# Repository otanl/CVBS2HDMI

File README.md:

# CVBS2HDMI — composite NTSC to HDMI on a Tang Nano 20K

English | [日本語](README.ja.md)

**v0.1**

> **Status.** What has been tested is the firmware together with the board as built, v0.1
> (tag `v0.1`). The board design now in `hardware/` is **v0.2, which has not been manufactured or
> tested**. If you make a board, either accept that, or use the v0.1 design from the tag.

CVBS2HDMI digitises composite NTSC video (CVBS) with an 8-bit ADC (AD9280), decodes it in colour on the
Tang Nano 20K's FPGA, and sends it to the on-board HDMI connector as 640×480p. There is no frame
buffer. Everything is built with an open-source toolchain (Yosys / nextpnr-himbaechel / Apicula /
openFPGALoader / Icarus Verilog); development was done on macOS.

## Features

- Colour NTSC decoding (240p and 480i) to 640×480p HDMI (DVI-compatible)
- 25.2 MSPS, one sample per clock, with no multipliers or ALU cells; the colour burst's phase
  is measured on every line with a CORDIC
- 240p, as most game consoles send it, holds still: the output frame switches between 524 and
  525 lines to match
- A broken or missing input is shown as noise, never as a black screen
- S2 zooms the picture 1.5 times and crops the border (a ring buffer of lines, no frame buffer)
- Eight glitch effects on the knobs of an M5Stack Unit 8Angle, each breaking a stage of the
  decoder itself
- Regression tests in simulation for every feature (`make test`)

Not supported: PAL, audio, black-level correction for 7.5 IRE setup.

## Hardware

- **Tang Nano 20K** (GW2AR-LV18QN88C8/I7)
- **Carrier board** (`tangADC`): an AD9280ARS and its input circuit, taking the Tang Nano 20K in
  a DIP-40 socket
  - Input: RCA → 75 Ω termination → ESD protection → 1 µF AC coupling → 20 Ω + 100 pF → AIN
  - AD9280: internal 2 V reference, single-ended input (0..2 V), clocked at 25.2 MHz by the FPGA
  - DC restoration is digital (black level measured on the front porch); the analog clamp is
    not used
  - Powered from the Tang Nano 20K's 3.3 V, with separate analog and digital rails through
    ferrite beads
- **Optional**: M5Stack Unit 8Angle (Grove J4/J5, I²C)

The carrier board's KiCad 10 project is in `hardware/`: schematic, PCB, and the JLCPCB
production files (BOM, placement, gerbers). They are at v0.2, the next revision, which has not
been manufactured; the board as built and measured is tag `v0.1`. `docs/pcb-respin.md` §4.6 and
§4.7 list the changes. Every part JLCPCB places is from its Basic or Preferred library.

Pin assignment (the single source is `constraints/tangnano20k_adc_probe.cst`):

| Signal | FPGA pin | | Signal | FPGA pin |
|---|---|---|---|---|
| `adc_clk` | 73 | | `adc_d[4]` | 29 |
| `adc_clamp` | 74 | | `adc_d[5]` | 30 |
| `adc_d[0]` | 27 | | `adc_d[6]` | 75 |
| `adc_d[1]` | 28 | | `adc_d[7]` | 77 |
| `adc_d[2]` | 72 | | `adc_otr` | 71 |
| `adc_d[3]` | 76 | | I²C SCL / SDA | 48 / 49 |

The data bus is not in physical pin order. The board's revision history, the pins that must not
be used, and the fixes planned for the next revision are in `docs/pcb-respin.md` (Japanese).

**Caution**: pin 3 of the Grove connectors is 5 V. A device that pulls I²C up to 5 V puts 5 V
on the FPGA's pins. The 8Angle pulls up to its own 3.3 V and is safe.

**Caution**: ADC bits 0, 1, 4 and 5 (pins 27..30) share an I/O bank with HDMI. Stock Apicula
packs those inputs as LVDS receivers, so every build must go through `scripts/gowin_pack_io.py`
(the Makefile does).

## Usage

### Installing the tools (once)

```sh
./scripts/setup-macos.sh
make check-tools
```

This installs the OSS CAD Suite into `.tools/oss-cad-suite`; your shell's PATH and macOS
settings are left alone.

### Building and loading

```sh
make ntsc                # build
make ntsc-program        # load into SRAM (lost at power-off)
make ntsc-flash          # write to flash (kept across power cycles)
```

`make program` loads not the HDMI decoder but the ADC probe used to bring up a board (see below).

### Buttons and LEDs

- **S1**: toggles the diagnostic view (waveform and bars). The black-and-white cells showing the
  ADC interface's state appear only at the bottom of this view.
- **S2**: toggles the 1.5× zoom, which scales up the middle of the picture and crops the border
  (for sources such as game consoles whose picture sits small inside a wide border). Both axes
  scale alike, so the aspect ratio is kept. After a switch the picture slides into place over
  about 1.5 seconds.
- **LEDs** (active low): 0 heartbeat, 1 PLL locked, 2 horizontal sync locked, 3 vertical sync
  seen, 4 and 5 the luma gain step

An input that cannot be synced (a broken signal, a wrong standard, an unplugged cable) does not
black out the screen: the signal is shown as it arrives, as noise, and a good signal is locked
again as soon as it returns. 240p (262 lines every field, 60.05 Hz), as most game consoles send
it, is shown by measuring the field length and switching the output frame between 525 and 524
lines.

### M5Stack Unit 8Angle (glitch effects)

Connect an M5Stack Unit 8Angle to Grove J4 or J5 and its eight knobs and switch are read
continuously over I²C (address 0x43, 100 kHz). Near the bottom of the S1 diagnostic view, each
knob is drawn as a cyan bar, the switch as a green block, and a red block shows while the unit
is not answering. `make sim-angle8` checks the reader against a model of the unit.

The eight knobs control **glitch effects**. They do not post-process the image; each one breaks
a stage of the decoder itself. A knob turned fully left is off, and with all knobs left the
picture is the clean one. The effects are enabled with the switch in the green position (as the
diagnostic view shows it).

Knobs 1..4 break **where lines go and their shape**, 5..8 break **colour**; each group is in the
order the signal passes through the decoder.

| Knob | What breaks |
|---|---|
| 1 | Sync slicing: dark parts of the picture read as sync, so the picture decides where lines start |
| 2 | Horizontal hold: real syncs are ignored and the line timing free-runs off frequency (sideways drift, diagonal tearing) |
| 3 | Line stretch: lines at random are stretched to twice the width or squeezed to half, leaving an older line behind |
| 4 | Line buffer: lines stop being updated, and old lines smear downwards |
| 5 | ADC bus faults: the faults this board really had, in order (pair misreads → stuck bits → crossed wiring) |
| 6 | Colour reference collapse: the burst is measured inside the picture and the oscillator drifts, so the hue jumps and rainbow stripes roll |
| 7 | Colour matrix overflow: the YUV→RGB gain is raised and the clipping removed, so bright and saturated parts fold into their complements (neon, solarised) |
| 8 | HDMI link failure: first the lanes skew, splitting red, green and blue sideways with a per-line shiver; past half way, blocks of a few lines lose a colour lane or misread it (inverted and so on). Worked out in the FPGA as the monitor would show it, so the link never drops |

`make sim-video-glitch` checks that each effect breaks the picture and that the picture is clean
again once the effect is removed. `make sim-link` checks, line by line, that the HDMI link
failure breaks the picture only in the ways it is allowed to.

### Sources with no sync step

A signal whose sync tip sits at blanking level (an early M5 setup, for example) needs a build
with different window positions. It is not switched automatically.

```sh
make ntsc-legacy
make ntsc-legacy-program
```

On a source with a sync step, the default (`LEGACY_TIMING=0`) measured 0.43% dropped rows and
colour on 120/120 frames, against 47.8% and 0/120 for `LEGACY_TIMING=1` (2026-09-24, same seed).

### Going back to a known-good version

The version verified on 2026-09-26 (tag `good-2026-09-26`) is kept as a bitstream,
`bitstreams/ntsc_good_2026-09-26.fs.gz`, so it can be written back whatever happens to the
sources or the toolchain.

```sh
make restore-flash       # write it to flash (kept across power cycles)
make restore-program     # load it into SRAM only (to try it)
git checkout good-2026-09-26   # the sources as they were
```

## Tests

```sh
make test                # everything (a few minutes)
make sim-video           # NTSC-J 75% bars, three fields, vertical interval included
make sim-zoom            # the 1.5× zoom (240p and interlaced, with a negative control)
make sim-video-glitch    # each glitch effect breaks the picture, and removing it restores it
make sim-link            # the HDMI link failure effect
make sim-hdmi            # TMDS encoding, line buffer races, start-up and video timing
```

`make test` includes negative controls: each bench also has to recognise a deliberately broken
setup as broken.

## Development and diagnostics

The decisions and measurements made during development are recorded in `CLAUDE.md`. When the
hardware behaves unexpectedly, search there first.

### Picture quality

```sh
make sim-reference       # every phase, ±100 ppm, half-wave burst, signal loss
make sim-tracking        # colour phase from the first line after 24 lines without burst
make sim-video-weak      # small sync amplitude
make sim-video-mono      # monochrome input with no burst
make sim-video-late      # recovery from a horizontal sync that arrives late
```

PNG captures of the HDMI output can be scored with the Python standard library and FFmpeg:

```sh
python3 scripts/video_quality.py 'build/cap*.png' --rows 20:350 --start 24 --bar-width 80
```

It reports, separately, rows in luma order, rows with a dark first bar, rows with colour, RGB
saturation, and row-to-row colour variation. The grey staircase in the bottom quarter is left out;
compare only captures of the same region and test pattern. The first capture after programming
is affected by the link and the vertical position re-acquiring, so always capture twice and score
the second, the same way for both sides of a comparison. Frames with no signal are counted too.
Bars in luma order do not prove that hue or amplitude is right.

With no UART, ADC values can be measured from the waveform view on HDMI:

```sh
make ntsc-scope-program             # starts in the full-range waveform and diagnostic view
# compare a phase: make ntsc-scope-program NTSC_SCOPE_PHASE=4
./scripts/live_capture.sh build/scope_new 120 8 --scope-mode 0 --phase 2
python3 scripts/scope_trace.py build/scope_new_012.png --trace-only --require-mode 0
# check the display path with a known ramp: make ntsc-scope-program NTSC_SCOPE_RAMP=2
make ntsc-program                   # back to the normal picture
```

To look at a signal that has no usable sync, capture raw ADC data without waiting for sync:

```sh
make ntsc-scope-program NTSC_SCOPE_RAMP=3 NTSC_SCOPE_FREERUN=1
./scripts/live_capture.sh build/raw_free_new 12 3 --scope-mode 3 --phase 2
python3 scripts/scope_trace.py build/raw_free_new_012.png --trace-only --require-mode 3
```

The normal capture waits for sync, and when none is found its buffer is never written, so zeros
that were never captured can be mistaken for measurements. `NTSC_SCOPE_FREERUN=1` captures every
66 ms or so regardless of sync, and the build gets its own name. `make sim-scope-freerun` checks
that all 2048 points are captured and re-captured with no sync, and that the sync-waiting mode
does not capture.

The waveform is drawn at 640×480 with three samples a pixel, and values are recovered from the
height of the red and white trace. The diagnostic build's vertical axis shows all 256 codes; to
read the S1 view of the normal build, pass `--legacy-scale` (there, codes above about 150 are
hidden behind the bars at the top). Ambiguous columns are dropped. This is an approximate
measurement from the screen, not a dump of every sample. Rows 200..207 of the diagnostic view
carry the mode, the ADC phase and a frame counter. `live_capture.sh` always captures at least
twice and checks the mode, the phase and that the counter advances; each time it sets aside the
first 120 frames as warm-up and measures the requested number after them. It never filters out
bad frames from the measured run. Each attempt is kept in its own folder and existing images are
never overwritten (use a new prefix). On the normal picture only pixel changes are checked:
without the diagnostic counter, a still picture cannot be told from a frozen capture, nor the
loaded bitstream identified. Amplitudes of oscillating parts are not validated; use
`--trace-only`, and do not use these readings to set colour gain.

### Recording the input and replaying it in simulation

The waveform view shows one sample in three; this records 32768 consecutive raw ADC samples
(about 20 lines) exactly, without the UART.

```sh
make ntsc-tape-program                                  # record once, freeze, show as grey cells
python3 scripts/live_capture.py build/tape 12 8
python3 scripts/tape_decode.py build/tape.hex build/tape_0*.png   # vote across 12 frames
python3 scripts/tape_trim.py build/tape.hex sim/my_tape.hex 18    # cut to an even number of lines
./scripts/tool iverilog -g2012 -s replay_tb -o build/replay_tb \
    src/ntsc_capture.v src/adc_front.v src/sync_lpf.v src/burst_nco.v src/cordic_atan.v \
    src/chroma_sincos.v sim/gowin_prim_sim.v sim/replay_tb.v
./scripts/tool vvp build/replay_tb +stim=sim/my_tape.hex +nsamp=<samples> +lines=400 +out=build/replay.txt
python3 scripts/replay_quality.py build/replay.txt --png build/replay.png  # same scale as the board
python3 scripts/tape_reference.py sim/my_tape.hex                          # floating-point reference decode
```

`replay_quality.py --frames 'build/cap_*.png'` scores captures from the board on the same scale.
`make sim-tape` checks the recording display and its decoder end to end against a known memory
image.

**With the M5 as the source, correctly decoded bars are not in luma order** (the M5 itself sends
yellow < cyan, green < magenta, red < blue). To evaluate with the M5, compare `replay_quality.py`'s
hue error and line-to-line variation with `tape_reference.py`'s values instead of
`video_quality.py`'s "correct rows".

## ADC probe (for bringing up a board, 27 MSPS)

A separate design for the first check on a new board: that the ADC's data is captured correctly.

Measured in step 1:

```
ADC ph=2 tog=FF min=96 max=255 thr=115 ln=1716 lmin=1715 lmax=1717 ok=15734 lns=15734 vs=60 otr=0 lk=1
```

A raw waveform (taken with `make autodump-program`, saved as `sim/ntsc_line_capture.hex`):

| Quantity | Measured | NTSC | Error |
| --- | --- | --- | --- |
| Sync tip | code 98 (±1) | — | — |
| Sync width | 4.59 us | 4.70 us | -2.3% |
| Blanking | code 133.9 | — | — |
| Sync to blanking | 282 mV | 286 mV | **-1.3%** |
| Burst start | 5.19 us after the sync edge | 5.3 us | — |
| Burst length | 2.52 us / **9.02 cycles** | 2.51 us / 9 cycles | **+0.2%** |
| Line period | **1716** samples | 1716.05 | — |

Counting exactly nine burst cycles shows that the sample clock and the subcarrier are in the right
time relation, and an amplitude error of -1.3% shows that the gain is right.

### Simulating

A synthetic NTSC signal goes through a behavioural model of the AD9280 and the line period is
measured.

```sh
make sim           # positive: must measure ln=1716
make sim-badphase  # negative: a wrong sampling phase must be reported as broken
```

The negative case exists to show that `ln=1716` is not a value that comes out whatever goes in.

### Loading it and measuring

```sh
make program   # load into SRAM (lost at power-off)
make monitor   # read the report
```

One line a second at 115200 8N1:

```
ADC ph=2 tog=FF min=79 max=205 thr=94 ln=1716 lmin=1716 lmax=1717 ok=15720 lns=15734 vs=60 otr=0
```

| Field | Meaning | Healthy value |
| --- | --- | --- |
| `ph` | sampling phase; 0..3 = 0 / 9.3 / 18.5 / 27.8 ns after the adc_clk rising edge | `2` |
| `tog` | OR of the bits that changed during the window | `FF` |
| `min` | lowest code → the sync tip level | about 70..90 |
| `max` | highest code → peak white | about 190..215 |
| `thr` | the sync slicing threshold actually used | min + a few tens |
| `ln` | the latest line period (samples) | **1716** |
| `lmin` / `lmax` | range of accepted line periods | 1716..1717 |
| `ok` | lines whose period is within 1700..1732 | about `lns` |
| `lns` | accepted lines | about 15734 |
| `vs` | vertical syncs detected | about 60 |
| `otr` | samples the AD9280 flagged as over range | `0` |

**`ln=1716` is the decisive one.** One NTSC line (15734.264 Hz) sampled at 27 MHz is

```
27e6 / 15734.264 = 1716.05 samples
```

so a steady 1716 proves at once that **the ADC clock, the data bus's bit order and the sampling
phase are all right**. No other single figure says that much.

#### Buttons (probe)

* **S2 (pin 87)**: advance the sampling phase by one. If `ln` does not appear, try all four.
* **S1 (pin 88)**: dump 2048 raw samples from a sync edge in hex, for checking the bit order by
  eye. The sync tip (a run of low values), then the back porch, then the picture should be
  visible.

#### Diagnostic LEDs (active low, probe)

| LED | Meaning |
| --- | --- |
| 0 | heartbeat (the design is running) |
| 1 | PLL locked |
| 2 | line period in range |
| 3 | vertical sync detected |
| 4 | over range detected (input too large) |
| 5 | a data bit never changes (bad wiring and so on) |

### The analog clamp is off by default

The AD9280's clamp (CLAMP/CLAMPIN) is **not used**: on this board it does more harm than good.
C2 at 1 µF is larger than the AD9280's clamp amplifier is designed for, so each pulse leaves a
transient longer than a line, which spoils the next sync edge. Measured:

| Clamp | Result |
| --- | --- |
| off (default) | `ok = lns = 15734`, `vs=60`, `ln=1716`, perfect |
| gated on sync lock | about 72% good lines, lock oscillating at 1 Hz, `vs` erratic |

Without the clamp the input still biases itself inside the conversion range (sync tip at 98,
white at about 225, 30 codes below 255). The decoder measures the porch and restores DC
digitally. The sync tip is not the black level, so do not subtract it from the picture.

`make clampgated-program` brings the clamp back for experiments.

### Builds for isolating faults

For suspecting the analog side. The RTL is the same; only a constraint or a parameter differs.

```sh
make pullup-program    # weak pull-ups on the ADC inputs; min=max=255 means the ADC is not driving the bus
make clampon-program   # CLAMP held on: AIN pinned to CLAMPIN, measurable with no video
make clampoff-program  # CLAMP held off (for comparison)
make clkhigh-program   # adc_clk held at 3.3 V → TP4 should read about 3.3 V
make clklow-program    # adc_clk held at 0 V → TP4 should read about 0 V
make clkslow-program   # adc_clk at about 1 Hz → TP4 swings 0 ↔ 3.3 V on a meter
make program           # back to normal
```

`clk=` at the end of the report shows which clock mode the loaded bitstream has.

#### The pull test: finding a floating pin without touching the board

The most effective technique of the bring-up. Build the same design three ways, with no pull,
pull-up and pull-down, and compare the reported codes in binary. **A ~50 kΩ internal pull cannot
move a pin the ADC is really driving.** A bit that follows the pull is an open joint; a bit that
resists it is connected, one pin at a time.

```sh
make program && make monitor          # no pull
make pullup-program && make monitor   # pull-up
make pulldown-program && make monitor # pull-down
```

**The trap**: a test point measures the net, not the pin. TP4 shows a healthy clock even if the
AD9280's pin 15 is lifted, and FB2 shows 3.3 V even if pin 2 is. The pull test gets round this
electrically for every pin the FPGA can read.

If `min`/`max` stay at 0 with `clampon`, the cause is not the video signal but the ADC's
conversion, its reference or the clamp circuit. If the bus does not move with `clkslow` either,
the ADC is not responding to its clock.

#### AVDD and DRVDD come from different pins

Easy to miss: the AD9280's analog and digital supplies come from **different pins of the Tang
Nano**.

```
Tang Nano DIP pad 19 → +3V3 → FB1 → +3V3A → U1 pin 28 AVDD
Tang Nano DIP pad 25 →        FB2 → +3V3D → U1 pin 2  DRVDD
```

So **a healthy TP2 (VREF) does not prove that DRVDD is there**: VREF depends on AVDD alone.
Without DRVDD the digital outputs are never driven and the bus is dead. On the v0.1 board FB1 and
FB2 are leaded parts, easy to probe at both ends. (The next revision uses 0805 chip beads; probe
TP5 and TP6 on the ADC side and the module's 3V3 pins on the other.)

## HDMI output pitfalls

**Never put `DRIVE=` or `BANK_VCCIO=` on an LVDS25 constraint.** Sipeed's `.cst` for Gowin EDA
carries `DRIVE=3.5 BANK_VCCIO=3.3`; brought into the open-source flow, it builds, meets timing,
and produces a link **no sink locks to**, with no warning. Apicula's own
`examples/tangnano20k.cst` uses only `IO_TYPE=LVDS25 PULL_MODE=NONE`.

**The 20K's HDMI pins are true LVDS.** The 9K's are emulated, so `ELVDS_OBUF`/`LVDS25E` ported
as-is is rejected outright by Apicula. Use `TLVDS_OBUF`/`LVDS25`, with P on the pair's IOBA pin
and N on its IOBB pin (33/34, 35/36, 37/38, 39/40).

**Pass the pixel clock to `--freq`.** nextpnr applies `--freq` to every clock it does not
otherwise know, so passing the serial clock (135) fails the TMDS encoder's combinational path on
a timing violation that does not exist.

### When nothing comes out, compare with a known-good bitstream

Faster than reasoning. Load Sipeed's prebuilt `.fs` (fetched with `gh`) and you know at once
whether the board, cable and sink are fine. Build Apicula's `examples/DVI` with the same flow and
you also know that the open-source toolchain can drive this board's TLVDS; what is left is the
difference from your own sources.

## Common problems

* **The report is garbled**: macOS resets a `/dev/cu.*` port to 9600 baud when its last
  descriptor closes, so `stty -f PORT 115200` followed by `cat PORT` loses the setting.
  `make monitor` (`scripts/monitor.py`) sets the speed on the descriptor it reads from.
* **The board is not found**: use a USB-C cable that carries data, and connect directly, without
  a hub.
* **`unable to open ftdi device`**: close anything using the board's USB device (a serial
  monitor, for instance) and reconnect.
* **Starting over**: `make clean`, then `make build`.

## License

MIT License. See `LICENSE`.

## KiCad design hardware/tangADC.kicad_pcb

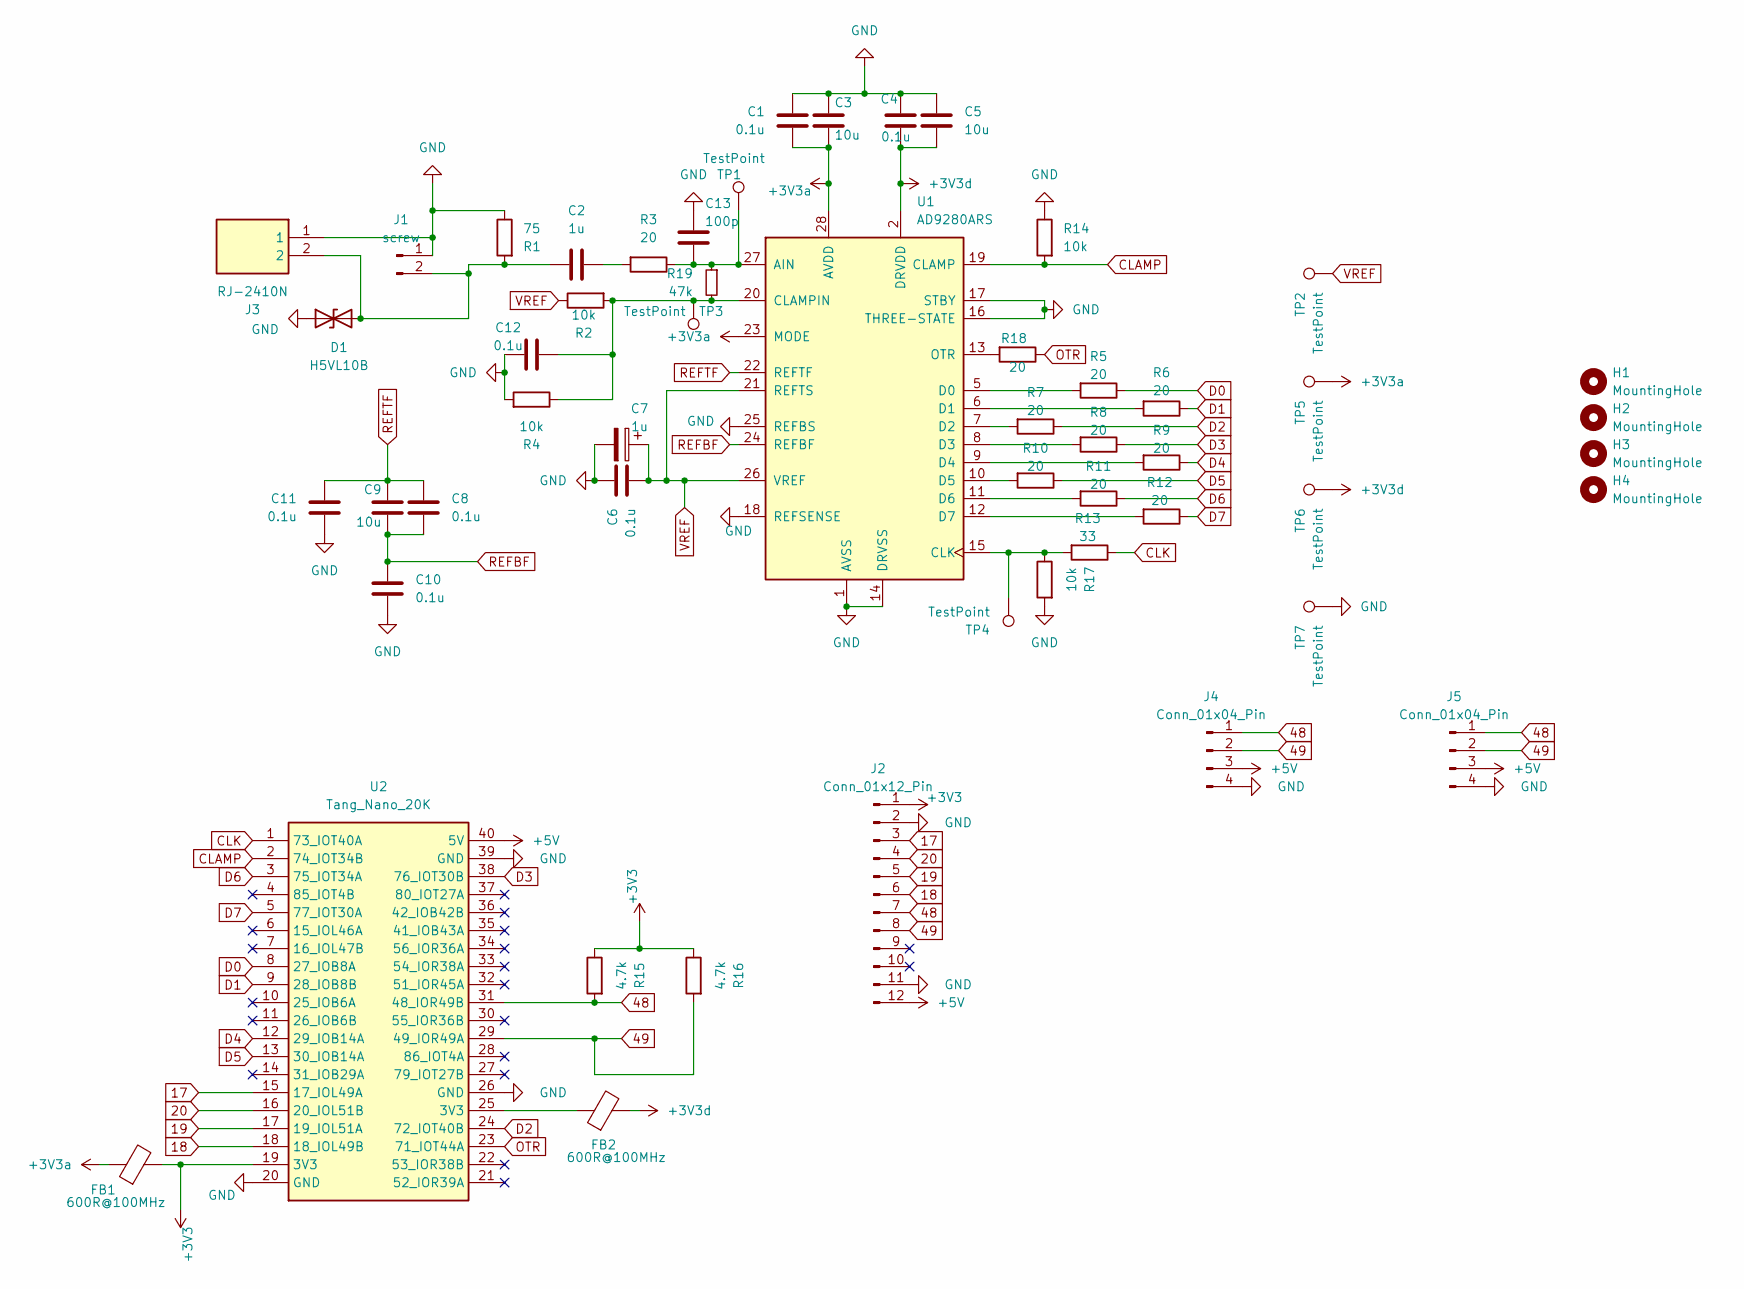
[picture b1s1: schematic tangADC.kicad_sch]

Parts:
C1, C4, C6, C8, C10, C11, C12: 0.1u; C_0603_1608Metric_Pad1.08x0.95mm_HandSolder
C2: 1u; C_0805_2012Metric_Pad1.18x1.45mm_HandSolder
C3, C5, C9: 10u; C_0805_2012Metric_Pad1.18x1.45mm_HandSolder
C7: 1u; CP_EIA-3216-10_Kemet-I_HandSolder
C13: 100p; C_0603_1608Metric_Pad1.08x0.95mm_HandSolder
D1: H5VL10B; D_SOD-882
FB1, FB2: 600R@100MHz; L_0805_2012Metric
H1, H2, H3, H4: MountingHole; MountingHole_2.7mm_M2.5
J1: screw; Altech_AK100_1x02_P5.00mm
J2: Conn_01x12_Pin; PinHeader_2x06_P2.54mm_Vertical
J3: RJ-2410N; RJ2410N; Manufacturer_Part_Number RJ-2410N
J4, J5: Conn_01x04_Pin; NS-Tech_Grove_1x04_P2mm_Vertical
R1: 75; R_0603_1608Metric
R2, R4, R14, R17: 10k; R_0603_1608Metric
R3, R5, R6, R7, R8, R9, R10, R11, R12, R18: 20; R_0603_1608Metric
R13: 33; R_0603_1608Metric
R15, R16: 4.7k; R_0603_1608Metric
R19: 47k; R_0603_1608Metric
TP1, TP2, TP3, TP4, TP5, TP6, TP7: TestPoint; TestPoint_THTPad_D1.0mm_Drill0.5mm
U1: AD9280ARS; SSOP-28_5.3x10.2mm_P0.65mm
U2: Tang_Nano_20K; DIP-40_TangNano20K

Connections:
17: J2.3, U2.15 (17_IOL49A)
18: J2.6, U2.18 (18_IOL49B)
19: J2.5, U2.17 (19_IOL51A)
20: J2.4, U2.16 (20_IOL51B)
48: J2.7, J4.1, J5.1, R15.2, U2.31 (48_IOR49B)
49: J2.8, J4.2, J5.2, R16.2, U2.29 (49_IOR49A)
+3V3: FB1.2, J2.1, R15.1, R16.1, U2.19 (3V3)
+3V3a: C1.1, C3.1, FB1.1, TP5.1 (1_1), U1.23 (MODE), U1.28 (AVDD)
+3V3d: C4.1, C5.1, FB2.2, TP6.1 (1_1), U1.2 (DRVDD)
+5V: J2.12, J4.3, J5.3, U2.40 (5V)
CLAMP: R14.2, U1.19 (CLAMP), U2.2 (74_IOT34B)
CLK: R13.1, U2.1 (73_IOT40A)
D0: R5.1, U2.8 (27_IOB8A)
D1: R6.1, U2.9 (28_IOB8B)
D2: R7.1, U2.24 (72_IOT40B)
D3: R8.1, U2.38 (76_IOT30B)
D4: R9.1, U2.12 (29_IOB14A)
D5: R10.1, U2.13 (30_IOB14A)
D6: R11.1, U2.3 (75_IOT34A)
D7: R12.1, U2.5 (77_IOT30A)
GND: C1.2, C3.2, C4.2, C5.2, C6.2, C7.2, C10.1, C11.1, C12.2, C13.2, D1.1 (A1), J1.1, J2.2, J2.11, J3.1, J4.4, J5.4, R1.1, R4.2, R14.1, R17.2, TP7.1 (1_1), U1.1 (AVSS), U1.14 (DRVSS), U1.16 (THREE-STATE), U1.17 (STBY), U1.18 (REFSENSE), U1.25 (REFBS), U2.20 (GND), U2.26 (GND), U2.39 (GND)
unnamed: C2.2, R3.2
unnamed: C2.1, D1.2 (A2), J1.2, J3.2, R1.2
unnamed: FB2.1, U2.25 (3V3)
unnamed: C13.1, R3.1, R19.1, TP1.1 (1_1), U1.27 (AIN)
unnamed: C12.1, R2.2, R4.1, R19.2, TP3.1 (1_1), U1.20 (CLAMPIN)
unnamed: R13.2, R17.1, TP4.1 (1_1), U1.15 (CLK)
unnamed: R5.2, U1.5 (D0)
unnamed: R6.2, U1.6 (D1)
unnamed: R7.2, U1.7 (D2)
unnamed: R8.2, U1.8 (D3)
unnamed: R9.2, U1.9 (D4)
unnamed: R10.2, U1.10 (D5)
unnamed: R11.2, U1.11 (D6)
unnamed: R12.2, U1.12 (D7)
unnamed: R18.2, U1.13 (OTR)
OTR: R18.1, U2.23 (71_IOT44A)
REFBF: C8.1, C9.1, C10.2, U1.24 (REFBF)
REFTF: C8.2, C9.2, C11.2, U1.22 (REFTF)
VREF: C6.1, C7.1, R2.1, TP2.1 (1_1), U1.21 (REFTS), U1.26 (VREF)

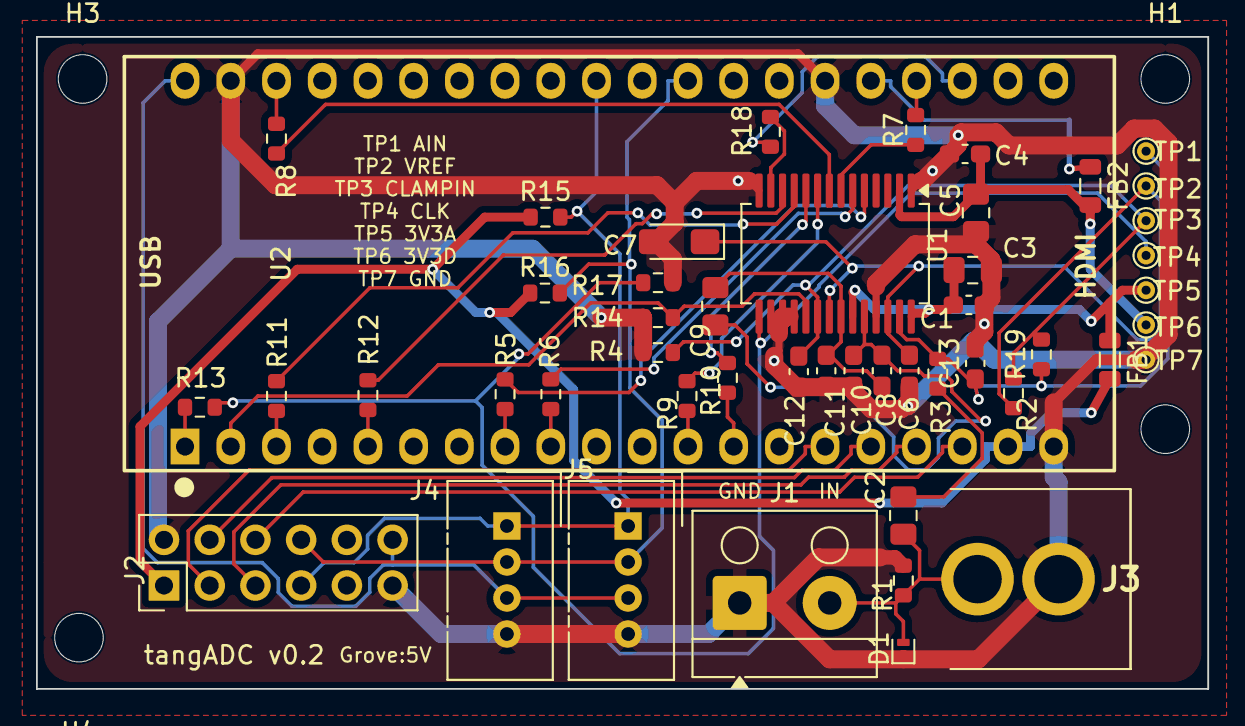
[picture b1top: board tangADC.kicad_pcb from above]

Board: 2 copper layers, 65.1 x 36.2 mm, 53 parts (0 on the bottom side), 40 nets.

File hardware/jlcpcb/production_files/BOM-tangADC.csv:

Comment,Designator,Footprint,LCSC,Quantity
0.1u,"C1,C10,C11,C12,C4,C6,C8",C_0603_1608Metric_Pad1.08x0.95mm_HandSolder,C14663,7
100p,C13,C_0603_1608Metric_Pad1.08x0.95mm_HandSolder,C14858,1
10k,"R14,R17,R2,R4",R_0603_1608Metric,C25804,4
10u,"C3,C5,C9",C_0805_2012Metric_Pad1.18x1.45mm_HandSolder,C15850,3
1u,C7,CP_EIA-3216-10_Kemet-I_HandSolder,C1848,1
1u,C2,C_0805_2012Metric_Pad1.18x1.45mm_HandSolder,C28323,1
20,"R10,R11,R12,R18,R3,R5,R6,R7,R8,R9",R_0603_1608Metric,C22950,10
33,R13,R_0603_1608Metric,C23140,1
4.7k,"R15,R16",R_0603_1608Metric,C23162,2
47k,R19,R_0603_1608Metric,C25819,1
600R@100MHz,"FB1,FB2",L_0805_2012Metric,C1017,2
75,R1,R_0603_1608Metric,C4275,1
H5VL10B,D1,D_SOD-882,C7420372,1
Tang_Nano_20K,U2,DIP-40_TangNano20K,,1
Conn_01x04_Pin,J4,NS-Tech_Grove_1x04_P2mm_Vertical,,1
Conn_01x04_Pin,J5,NS-Tech_Grove_1x04_P2mm_Vertical,,1
RJ-2410N,J3,RJ2410N,,1
TestPoint,TP7,TestPoint_THTPad_D1.0mm_Drill0.5mm,,1
TestPoint,TP6,TestPoint_THTPad_D1.0mm_Drill0.5mm,,1
TestPoint,TP1,TestPoint_THTPad_D1.0mm_Drill0.5mm,,1
TestPoint,TP5,TestPoint_THTPad_D1.0mm_Drill0.5mm,,1
TestPoint,TP4,TestPoint_THTPad_D1.0mm_Drill0.5mm,,1
TestPoint,TP3,TestPoint_THTPad_D1.0mm_Drill0.5mm,,1
TestPoint,TP2,TestPoint_THTPad_D1.0mm_Drill0.5mm,,1
AD9280ARS,U1,SSOP-28_5.3x10.2mm_P0.65mm,,1
screw,J1,Altech_AK100_1x02_P5.00mm,,1
Conn_01x12_Pin,J2,PinHeader_2x06_P2.54mm_Vertical,,1
